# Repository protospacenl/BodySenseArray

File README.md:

# BodySenseArray
Body Sensor Array

## Data transfer
Data transfer between sensor units uses RS485. Use a RS485 to usb converter to send data over to the PC.

Serial settings:
 * Baudrate: 250000
 * 8n1
 * no flow control

## Sensor data format
Each packet starts with a `%` start token and ends with a CRC. Check the crc to verify data integrity. If crc is not valid the received packet should be discarded.

 * byte order: little endian
 * format: `%<id><temperature><acc_x><acc_y><acc_z><gyro_x><gyro_y><gyro_z><crc>`

field | type
--- | ---
% | uint8_t
id | uint8_t
temperature | uint16_t
acc_[xyz] | int16_t
gyro_[xyz] | int16_t
crc | uint8_t

## CRC
CRC algorithm used is the [Dalles iButton 8-bit CRC](https://www.microchip.com/webdoc/AVRLibcReferenceManual/group__util__crc_1ga37b2f691ebbd917e36e40b096f78d996.html).

Example C implementation  (taken from above link):
```C
uint8_t
_crc_ibutton_update(uint8_t crc, uint8_t data)
{
    uint8_t i;

    crc = crc ^ data;
    for (i = 0; i < 8; i++)
    {
        if (crc & 0x01)
            crc = (crc >> 1) ^ 0x8C;
        else
            crc >>= 1;
    }
    
    return crc;
}
```
or in python (see [examples](https://github.com/protospacenl/BodySenseArray/blob/90c5e3de4db39f0ca5cd2b3785d3c42a4cba6765/examples/serial_read/serial_read.py#L60) for usage)
```python
def compute_crc(data):
    crc = 0x00
    for c in data[:-1]:
        crc = crc ^ c
        for i in range(0, 8):
            if crc & 0x01:
                crc  = (crc >> 1) ^ 0x8c
            else:
                crc = crc >> 1
    return crc
```

## Conversions
For efficiency the sensor data is in its integer form and needs to be translated to real world values. 
See the [examples](https://github.com/protospacenl/BodySenseArray/tree/master/examples) for implementation details.

### Temperature
```python
def temperature_from_raw(t):
    return t * 0.00390625
```

### acceleration
Translation from the raw acceleration values to *g*:
`(float)in * 0.061 * (g >> 1) / 1000.0`  
where *in* is the raw 16-bit two's complement value and *g* is the sensitivity (currently 2).

Range for 2g:
 - min: -1.99848g
 - max: 1.99787g

Example:
```python
def acc_from_raw(in, g=2):
    return in * 0.061 * (g >> 1) / 1000.
 ```

### angular rate
Translation from the raw angular rate to *dps*:
`(float)in * 4.375 * (dps / 125) / 1000.0`
where *in* is the raw 16-bit two's complement value and *dps* is the sensitivity (currently 2000).

Range for 2000dps:
 - min: -2293.76 dps
 - max: 2293.69 dps

Example:
```python
def dps_from_raw(in, dps=2000):
  return in * 4.375 * (dps / 125) / 1000.
```

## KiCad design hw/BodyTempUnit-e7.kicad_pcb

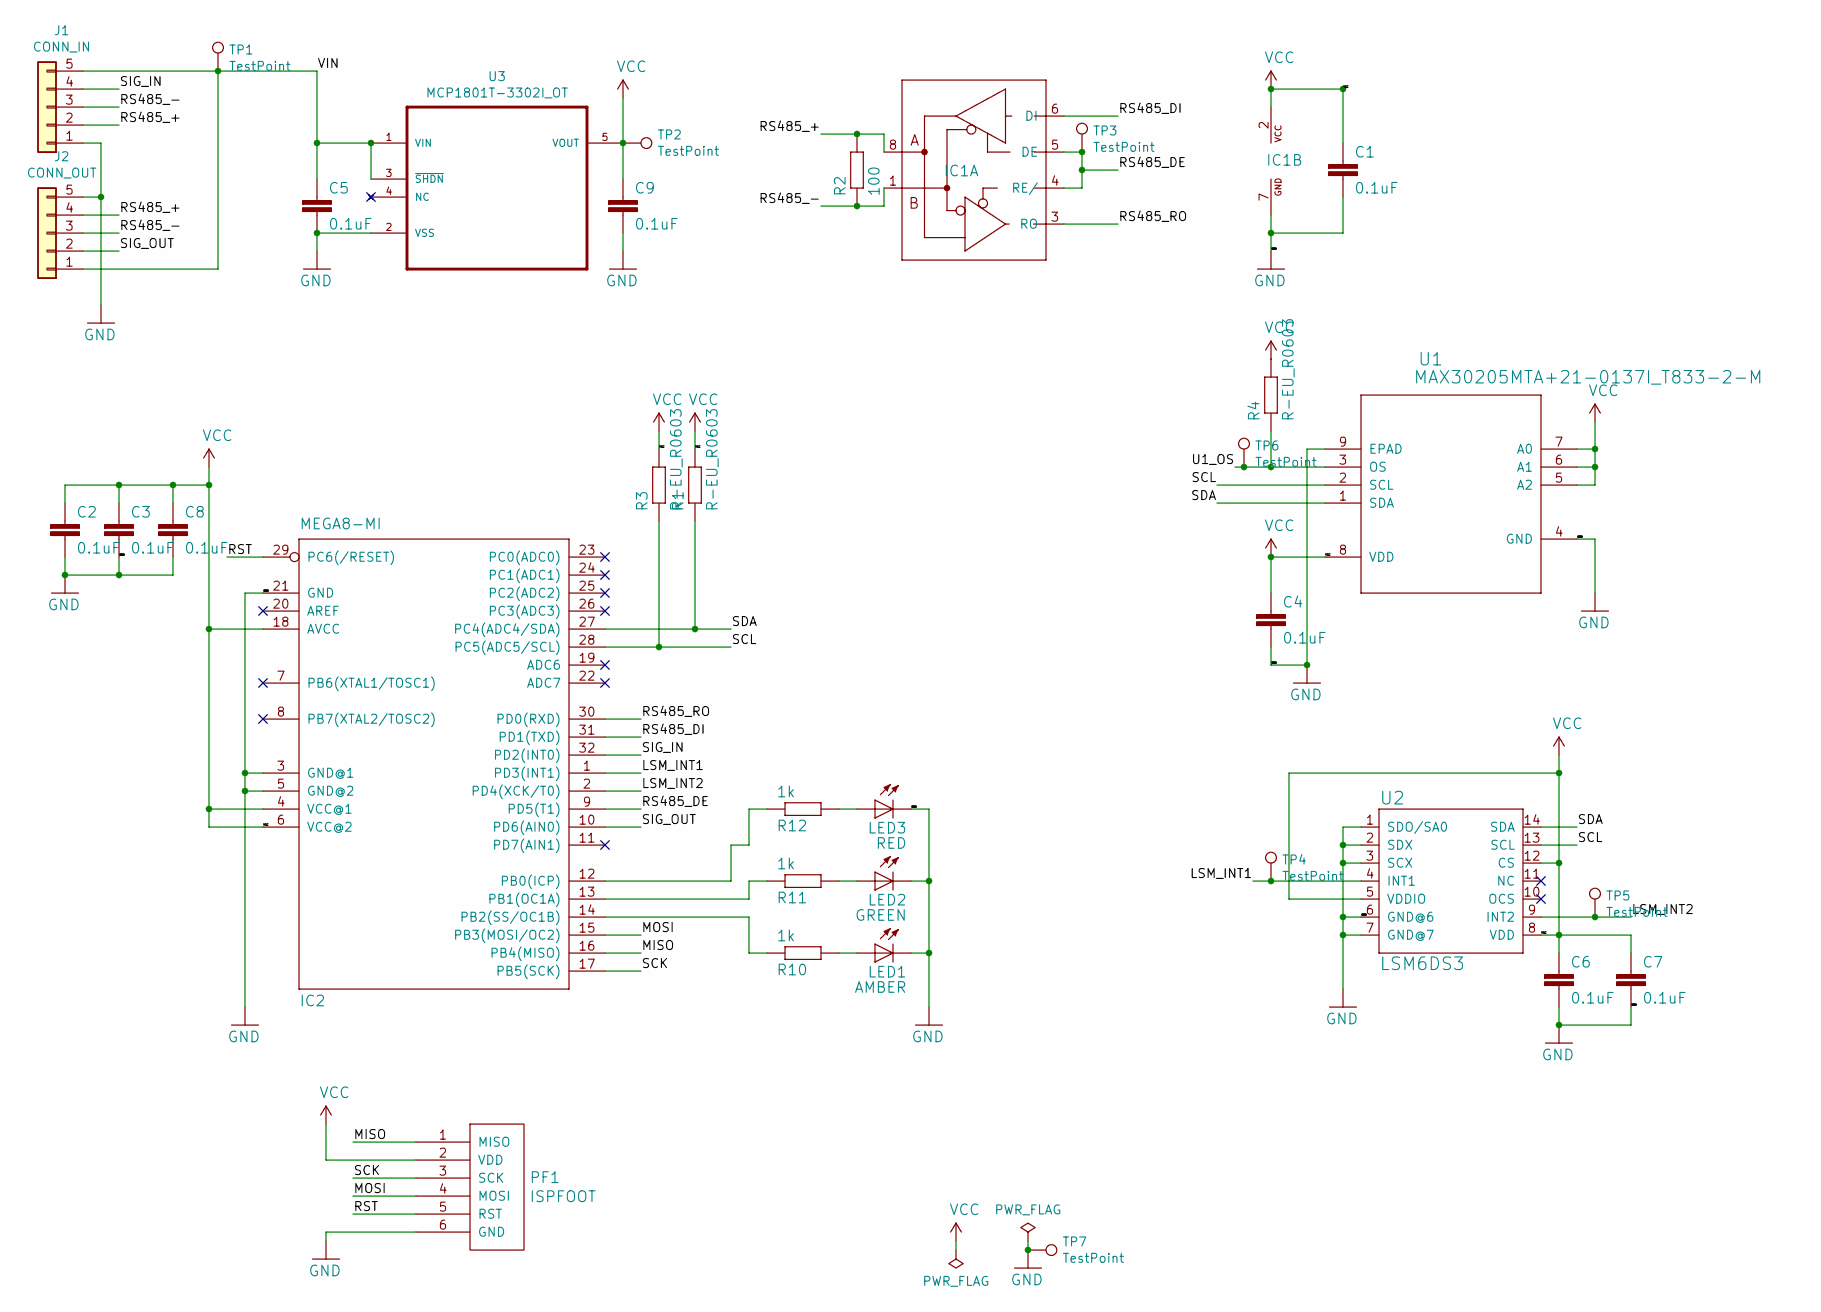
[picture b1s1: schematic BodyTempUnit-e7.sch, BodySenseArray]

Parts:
C1, C2, C3, C5, C6, C7, C8, C9: 0.1uF; C0603K
C4: 0.1uF; C_0402_1005Metric
IC1: MAX481CUA; UMAX8
IC2: MEGA8-MI; MLF32
J1: CONN_IN; Molex_PicoBlade_53261-0571_1x05-1MP_P1.25mm_Horizontal
J2: CONN_OUT; Molex_PicoBlade_53261-0571_1x05-1MP_P1.25mm_Horizontal
LED1: AMBER; CHIPLED_0603
LED2: GREEN; CHIPLED_0603
LED3: RED; CHIPLED_0603
PF1: ISPFOOT; Tag-Connect_TC2030-IDC-NL_2x03_P1.27mm_Vertical
R1, R3: R-EU_R0603; R0603
R2: 100; R0603
R4: R-EU_R0603; R_0402_1005Metric
R10, R11, R12: 1k; R0603
TP1, TP2, TP3, TP4, TP5, TP6, TP7: TestPoint; TestPoint_Pad_D1.0mm
U1: MAX30205MTA+21-0137I_T833-2-M; 21-0137I_T833-2-M
U2: LSM6DS3; LGA14L
U3: MCP1801T-3302I_OT; SOT-23-5

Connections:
/LSM_INT1: IC2.1 (PD3(INT1)), TP4.1, U2.4 (INT1)
/LSM_INT2: IC2.2 (PD4(XCK/T0)), TP5.1, U2.9 (INT2)
/MISO: IC2.16 (PB4(MISO)), PF1.1 (MISO)
/MOSI: IC2.15 (PB3(MOSI/OC2)), PF1.4 (MOSI)
/RS485_+: IC1.8 (A), J1.2, J2.4, R2.2
/RS485_-: IC1.1 (B), J1.3, J2.3, R2.1
/RS485_DE: IC1.4 (RE/), IC1.5 (DE), IC2.9 (PD5(T1)), TP3.1
/RS485_DI: IC1.6 (DI), IC2.31 (PD1(TXD))
/RS485_RO: IC1.3 (RO), IC2.30 (PD0(RXD))
/RST: IC2.29 (PC6(/RESET)), PF1.5 (RST)
/SCK: IC2.17 (PB5(SCK)), PF1.3 (SCK)
/SCL: IC2.28 (PC5(ADC5/SCL)), R3.1, U1.2 (SCL), U2.13 (SCL)
/SDA: IC2.27 (PC4(ADC4/SDA)), R1.1, U1.1 (SDA), U2.14 (SDA)
/SIG_IN: IC2.32 (PD2(INT0)), J1.4
/SIG_OUT: IC2.10 (PD6(AIN0)), J2.2
/U1_OS: R4.1, TP6.1, U1.3 (OS)
/VIN: C5.1, J1.5, J2.1, TP1.1, U3.1 (VIN), U3.3 (~SHDN)
GND: C1.2, C2.2, C3.2, C4.2, C5.2, C6.2, C7.2, C8.2, C9.2, IC1.7 (GND), IC2.3 (GND@1), IC2.5 (GND@2), IC2.21 (GND), IC2.33, J1.1, J2.5, LED1.C, LED2.C, LED3.C, PF1.6 (GND), TP7.1, U1.4 (GND), U1.9 (EPAD), U2.1 (SDO/SA0), U2.2 (SDX), U2.3 (SCX), U2.6 (GND@6), U2.7 (GND@7), U3.2 (VSS)
unnamed: IC2.12 (PB0(ICP)), R12.1
unnamed: IC2.13 (PB1(OC1A)), R11.1
unnamed: IC2.14 (PB2(SS/OC1B)), R10.1
unnamed: LED1.A, R10.2
unnamed: LED2.A, R11.2
unnamed: LED3.A, R12.2
VCC: C1.1, C2.1, C3.1, C4.1, C6.1, C7.1, C8.1, C9.1, IC1.2 (VCC), IC2.4 (VCC@1), IC2.6 (VCC@2), IC2.18 (AVCC), PF1.2 (VDD), R1.2, R3.2, R4.2, TP2.1, U1.5 (A2), U1.6 (A1), U1.7 (A0), U1.8 (VDD), U2.5 (VDDIO), U2.8 (VDD), U2.12 (CS), U3.5 (VOUT)

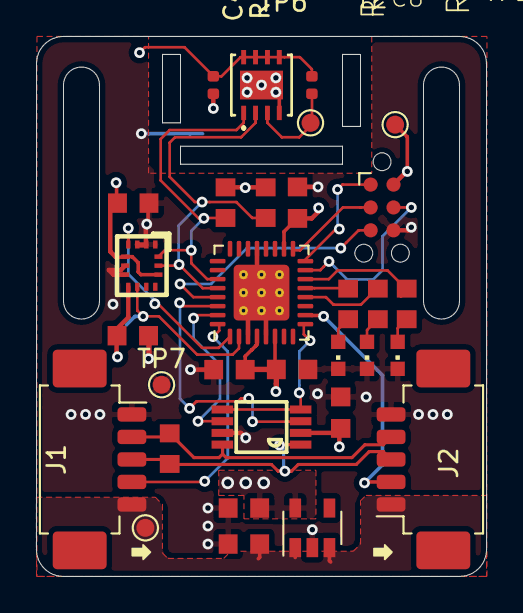
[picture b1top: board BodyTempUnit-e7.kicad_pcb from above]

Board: 4 copper layers, 25.0 x 30.0 mm, 34 parts (0 on the bottom side), 25 nets.

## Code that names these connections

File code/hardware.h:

/* 
 * File:   hardware.h
 * Author: simon
 *
 * Created on July 4, 2019, 11:52 PM
 */

#ifndef HARDWARE_H
#define	HARDWARE_H

#ifdef	__cplusplus
extern "C" {
#endif

#define F_CPU           8000000UL
#define RS485_BAUDRATE  250000
    
#define LED_RED         PB1
#define LED_GREEN2      PB0
#define LED_GREEN1      PB2
#define SIG_IN          PD2
#define SIG_OUT         PD6
#define RS485_DE        PD5
    
#define MAX30205_ADDR   0x4F    /* temperature sensor */
#define LSM6DS3_ADDR    0x6A    /* IMU accel / gyro */

#ifdef	__cplusplus
}
#endif

#endif	/* HARDWARE_H */

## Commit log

2019-06-04 Moved to hw folder
2019-06-06 Removed old files
2019-06-06 gitignore for eagle & kicad
2019-06-06 KiCad body sense array
2019-06-07 Few fixes in schematic
    * Power flags to gnd and vcc to avoid erc warning
    * Checked connections (OK)
    * Flaged nc connections accordingly to avoid erc warnings
    * Removed project specific symbol libs from global table
    * Connected RS485_DE to PD5
    * Moved LED3 from PD5 -> PD7
2019-06-07 Added PS worksheet
2019-06-07 GND pour added to mlf footprint
2019-06-07 switched regulator with RS485
2019-06-07 Added project file
2019-06-08 some rerouting
2019-06-08 Reroute ISP
2019-06-10 Routing mostly done
2019-06-10 Ready for final check
2019-06-11 All routed, final check pending
2019-06-13 version sent to production
2019-07-06 Added .gitignore entries for mplabX
2019-07-06 initial code commit
2019-08-08 Working gyro and acc
2019-08-10 Binary output
2019-08-10 Added jupiter-notebook example
2019-10-10 added pyvis wip example
2019-10-10 Increased accel sensitivity to 2g
2019-10-10 Placed ascii output under DEBUG define
2019-10-10 Realtime signal demo
2019-10-10 Moved bare serial read to own dir
2019-10-10 increased sensitivity to 2g for accelerometer
2019-10-10 Added pip requirements files
2019-10-10 Some nice formatting
